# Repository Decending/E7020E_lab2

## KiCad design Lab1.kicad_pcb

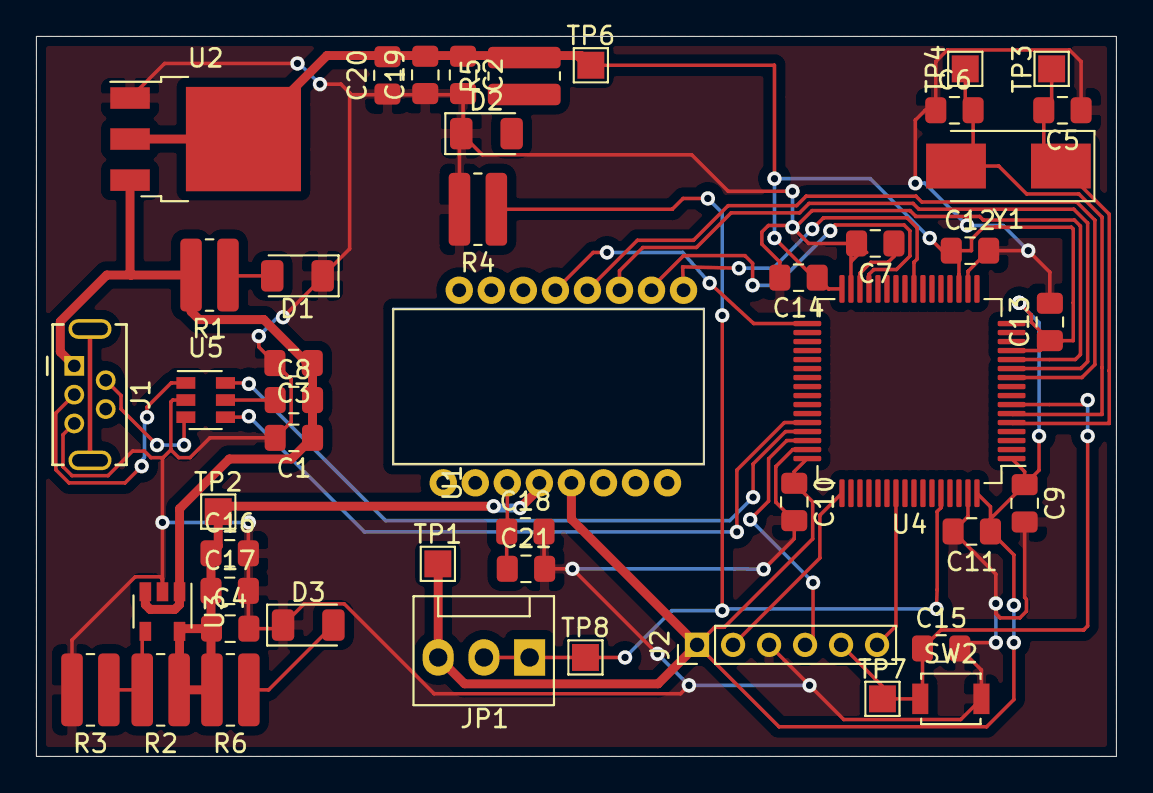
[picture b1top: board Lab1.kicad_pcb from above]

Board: 2 copper layers, 60.0 x 40.0 mm, 47 parts (0 on the bottom side), 27 nets.

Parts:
C1, C2, C21: 4u7; C_0805_2012Metric_Pad1.18x1.45mm_HandSolder
C3, C9, C10, C11, C12, C13, C14: 1u; C_0805_2012Metric_Pad1.18x1.45mm_HandSolder
C4: 2.2u; C_0805_2012Metric_Pad1.18x1.45mm_HandSolder
C5, C6: 22pF; C_0805_2012Metric_Pad1.18x1.45mm_HandSolder
C7: 4.7uF; C_0805_2012Metric_Pad1.18x1.45mm_HandSolder
C8, C15, C17, C18, C20: 100n; C_0805_2012Metric_Pad1.18x1.45mm_HandSolder
C16, C19: 10u; C_0805_2012Metric_Pad1.18x1.45mm_HandSolder
D1, D2, D3: Indicator LED; LED_1206_3216Metric
J1: USB_OTG; USB_Mini-B_Tensility_54-00023_Vertical
J2: SWD; PinHeader_1x06_P2.00mm_Vertical
JP1: DFU; FanPinHeader_1x03_P2.54mm_Vertical
R1: 1.5k; R_0815_2038Metric_Pad1.20x4.05mm_HandSolder
R2: 5.6k; R_0815_2038Metric_Pad1.20x4.05mm_HandSolder
R3, R4: 10k; R_0815_2038Metric_Pad1.20x4.05mm_HandSolder
R5: 820; R_0815_2038Metric_Pad1.20x4.05mm_HandSolder
R6: 47; R_0815_2038Metric_Pad1.20x4.05mm_HandSolder
SW2: Reset; SW_SPST_B3U-1000P
TP1, TP3, TP4, TP6, TP7, TP8: TestPoint; TestPoint_Pad_1.5x1.5mm
TP2: 1.9V; TestPoint_Pad_1.5x1.5mm
U1: PMW3389
U2: AP2125N-3.3TRG; TO-252-3_TabPin2
U3: MIC5235YM5-TR; SOT-23-5
U4: STM32F411RETx; LQFP-64_10x10mm_P0.5mm
U5: USBLC6-2SC6; SOT-23-6
Y1: 16Mhz; Crystal_SMD_0603-2Pin_6.0x3.5mm_HandSoldering

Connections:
+3V3: C2.1, C9.1, C10.1, C11.1, C12.1, C13.1, C14.1, C19.2, C20.2, J2.1, JP1.3, R5.2, TP1.1, TP6.1, U1.5, U2.2, U4.1, U4.13, U4.19, U4.32, U4.48, U4.64
+5V: C1.1, C3.1, C8.2, J1.1, R1.2, U2.3, U3.1, U3.3
BOOT0: JP1.1, JP1.2, R4.1, TP8.1, U4.60
GND: C1.2, C2.2, C3.2, C4.2, C5.1, C6.1, C7.2, C9.2, C10.2, C11.2, C12.2, C13.2, C14.2, C15.2, C16.2, C17.2, C18.2, C19.1, C20.1, C21.2, D1.1, D2.1, D3.1, J1.5, J2.3, R3.2, R4.2, SW2.2, U2.1, U3.2, U4.12, U4.18, U4.31, U4.47, U4.63, U5.2
IN_D+: J1.3, U5.1
IN_D-: J1.2, U5.3
MISO: U1.12, U4.10
MOSI: U1.11, U4.11
Motion: U1.9, U4.24
NCS: U1.13, U4.33
NRST: C15.1, J2.5, SW2.1, TP7.1, U4.7
unnamed: C5.2, TP3.1, U4.5, Y1.1
unnamed: C6.2, TP4.1, U4.6, Y1.2
unnamed: C7.1, U4.30
unnamed: C8.1, U5.5
unnamed: C18.1, C21.1, U1.3
unnamed: D1.2, R1.1
unnamed: D2.2, R5.1
unnamed: D3.2, R6.1
unnamed: R2.2, R3.1, U3.4
OUT_D+: U4.45, U5.6
OUT_D-: U4.44, U5.4
SCK: U1.10, U4.29
SWCLK: J2.2, U4.49
SWDIO: J2.4, U4.46
SWO: J2.6, U4.55
VDD: C4.1, C16.1, C17.1, R2.1, R6.2, TP2.1, U1.4, U3.5

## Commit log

2021-01-29 Initial upload - part 4 recently completed
    Might want to redo part 4, as the spaghetti might be a bit too much...
2021-02-02 Backup of working 1st prototype
2021-02-02 2nd design, quite happy with this one!
2021-02-03 Fixed decoupling capacitors
